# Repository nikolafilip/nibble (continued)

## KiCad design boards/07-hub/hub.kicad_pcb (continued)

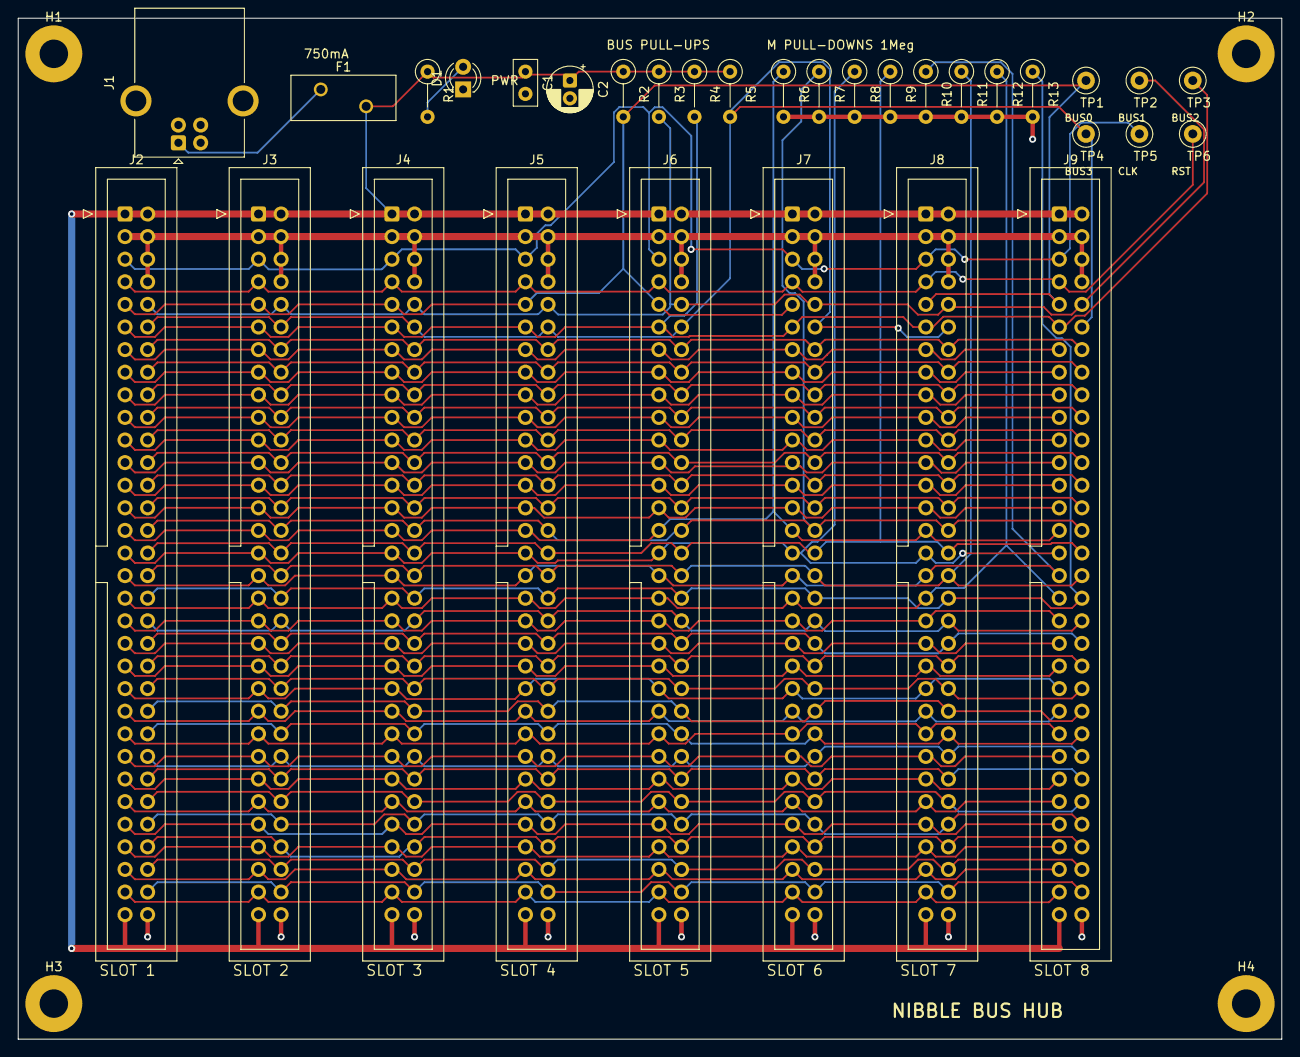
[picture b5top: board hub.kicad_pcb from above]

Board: 2 copper layers, 142.0 x 114.7 mm, 36 parts (0 on the bottom side), 60 nets.

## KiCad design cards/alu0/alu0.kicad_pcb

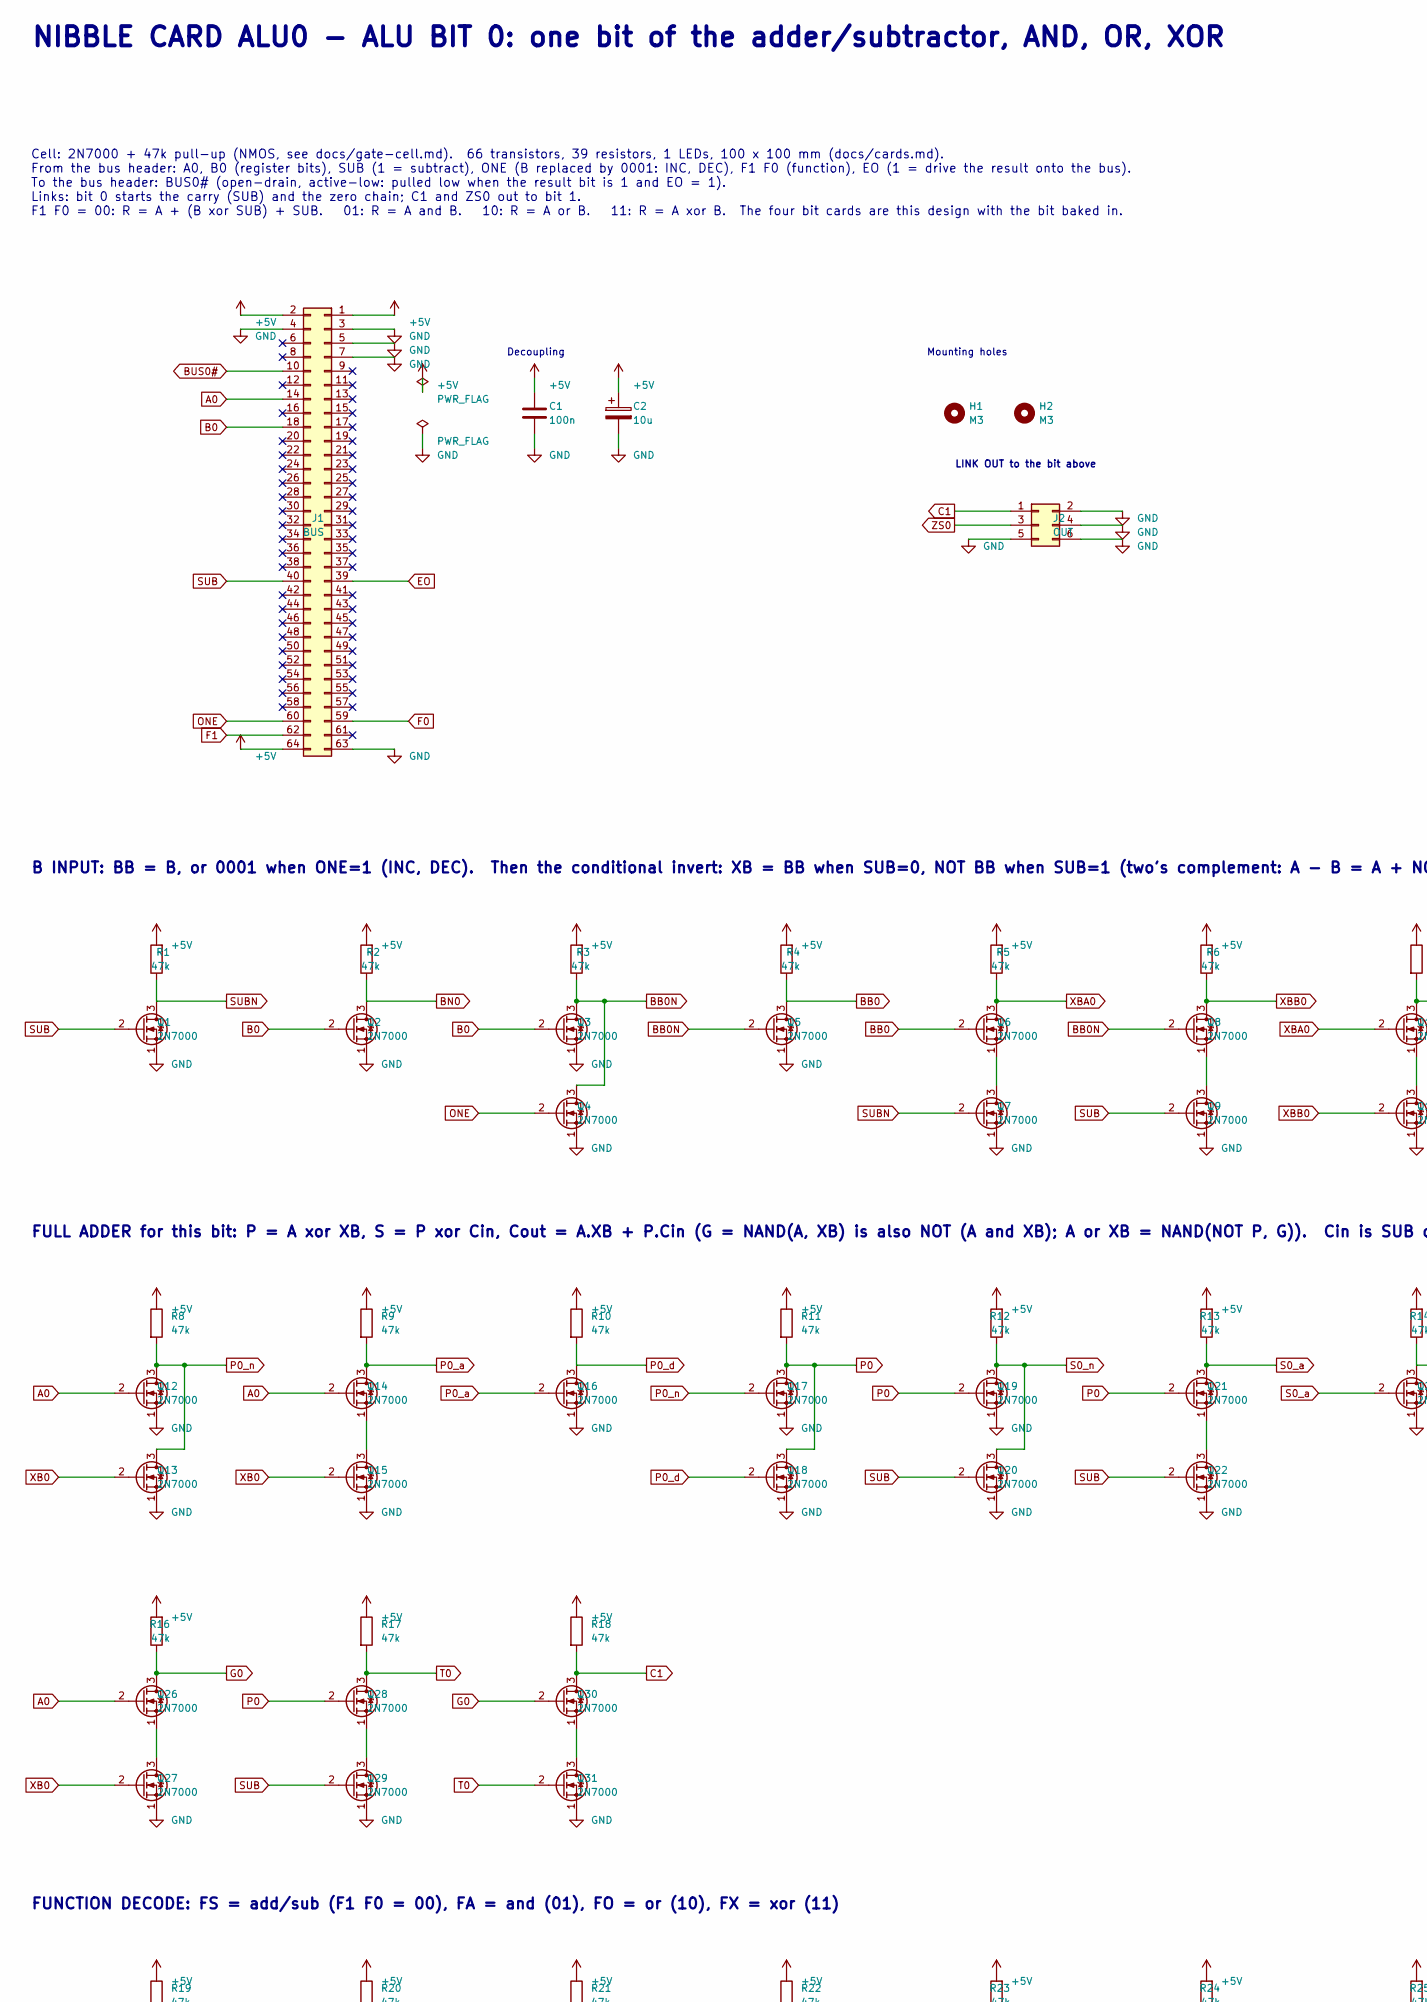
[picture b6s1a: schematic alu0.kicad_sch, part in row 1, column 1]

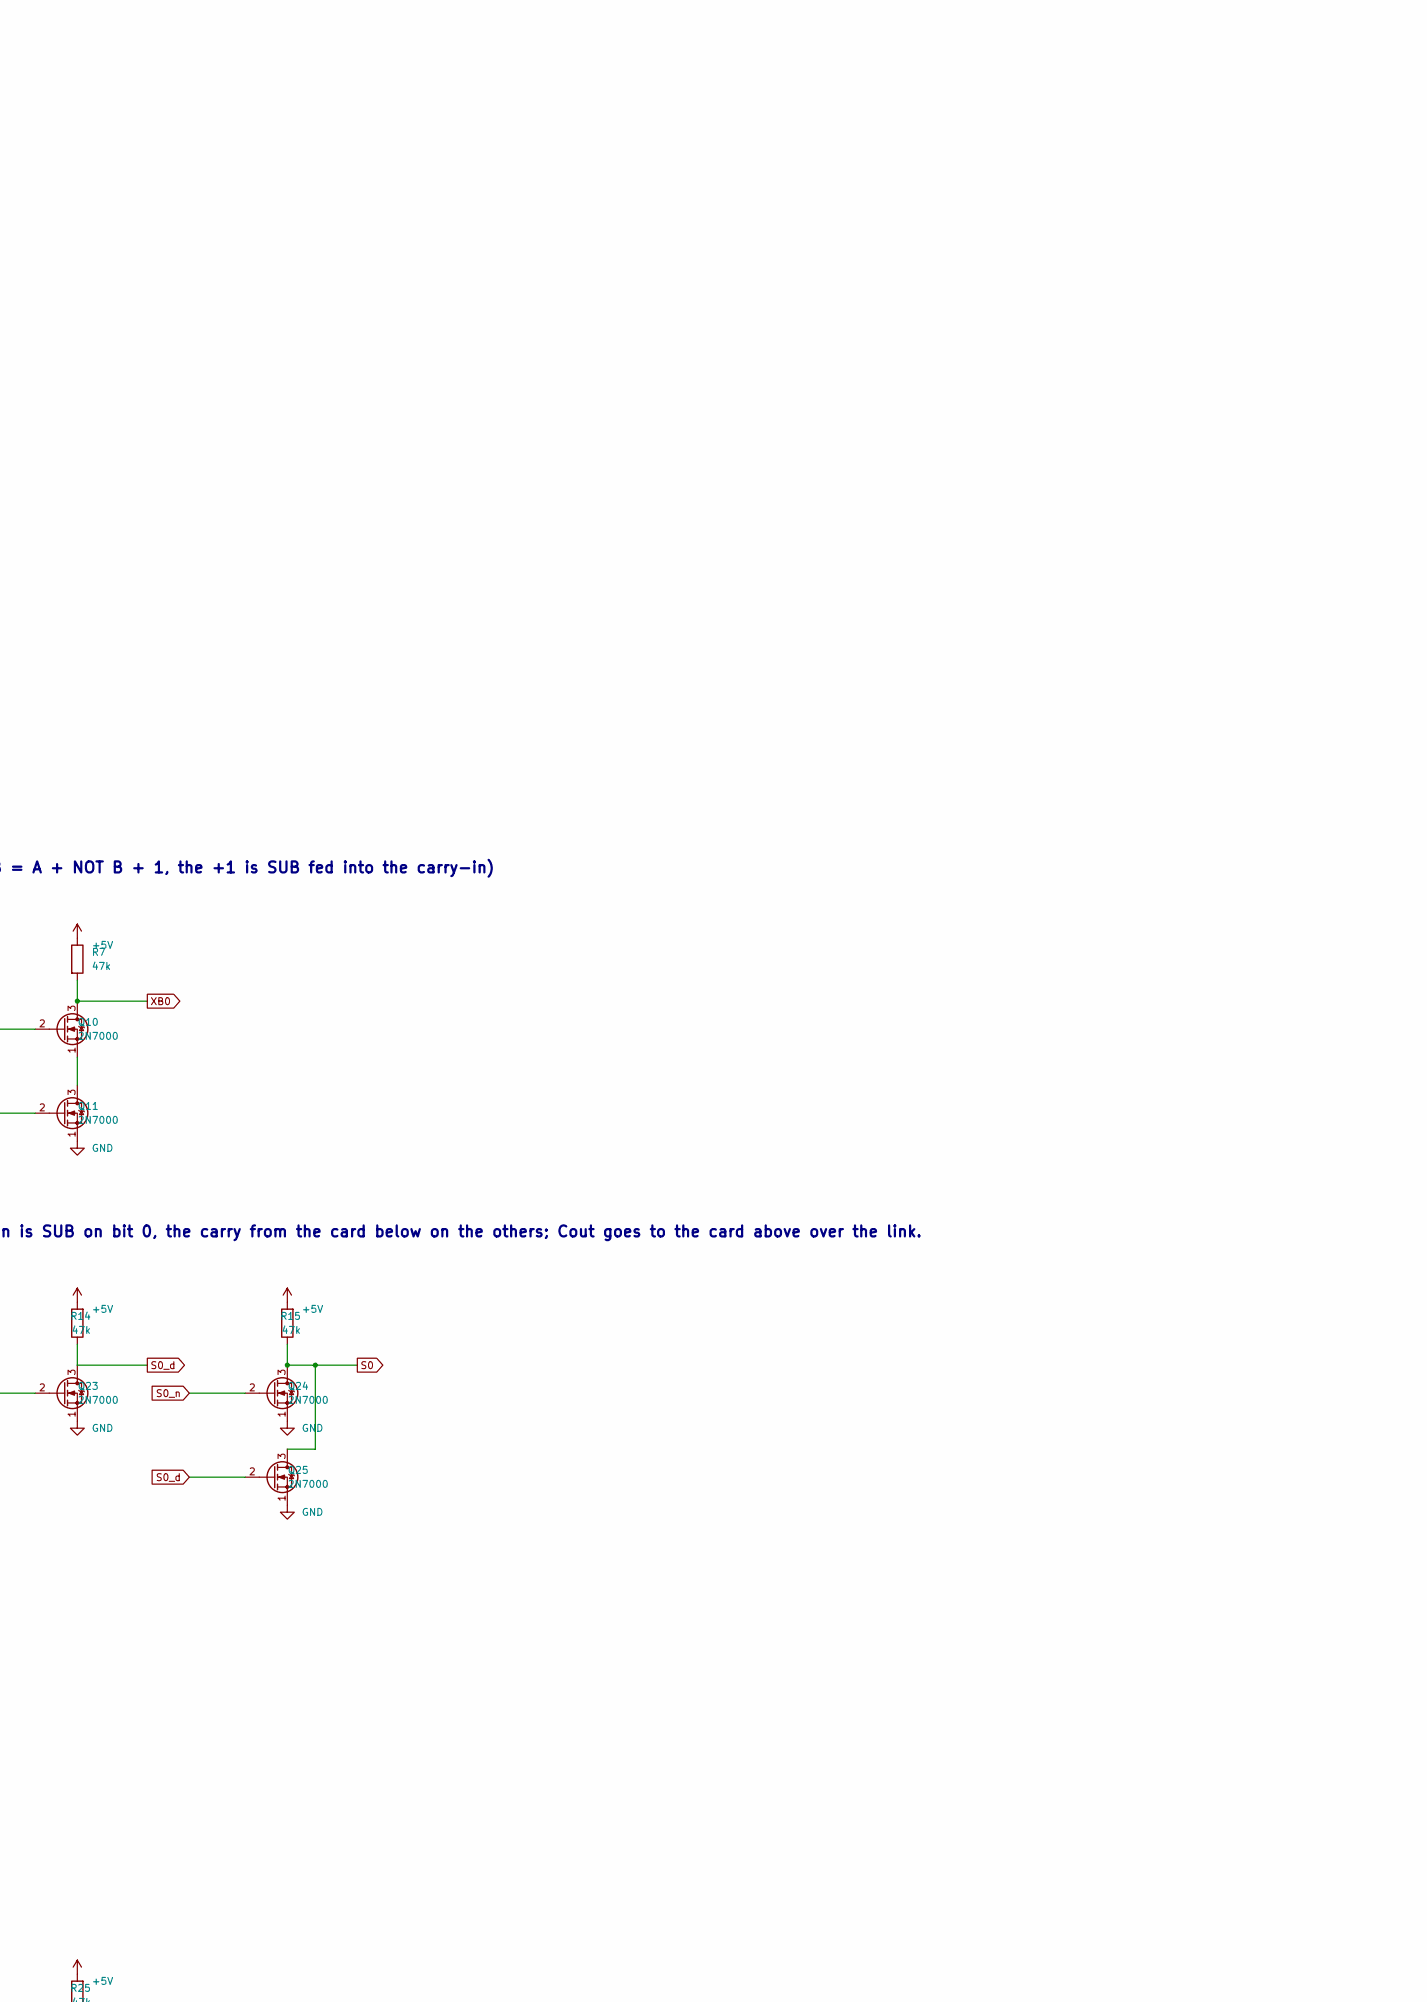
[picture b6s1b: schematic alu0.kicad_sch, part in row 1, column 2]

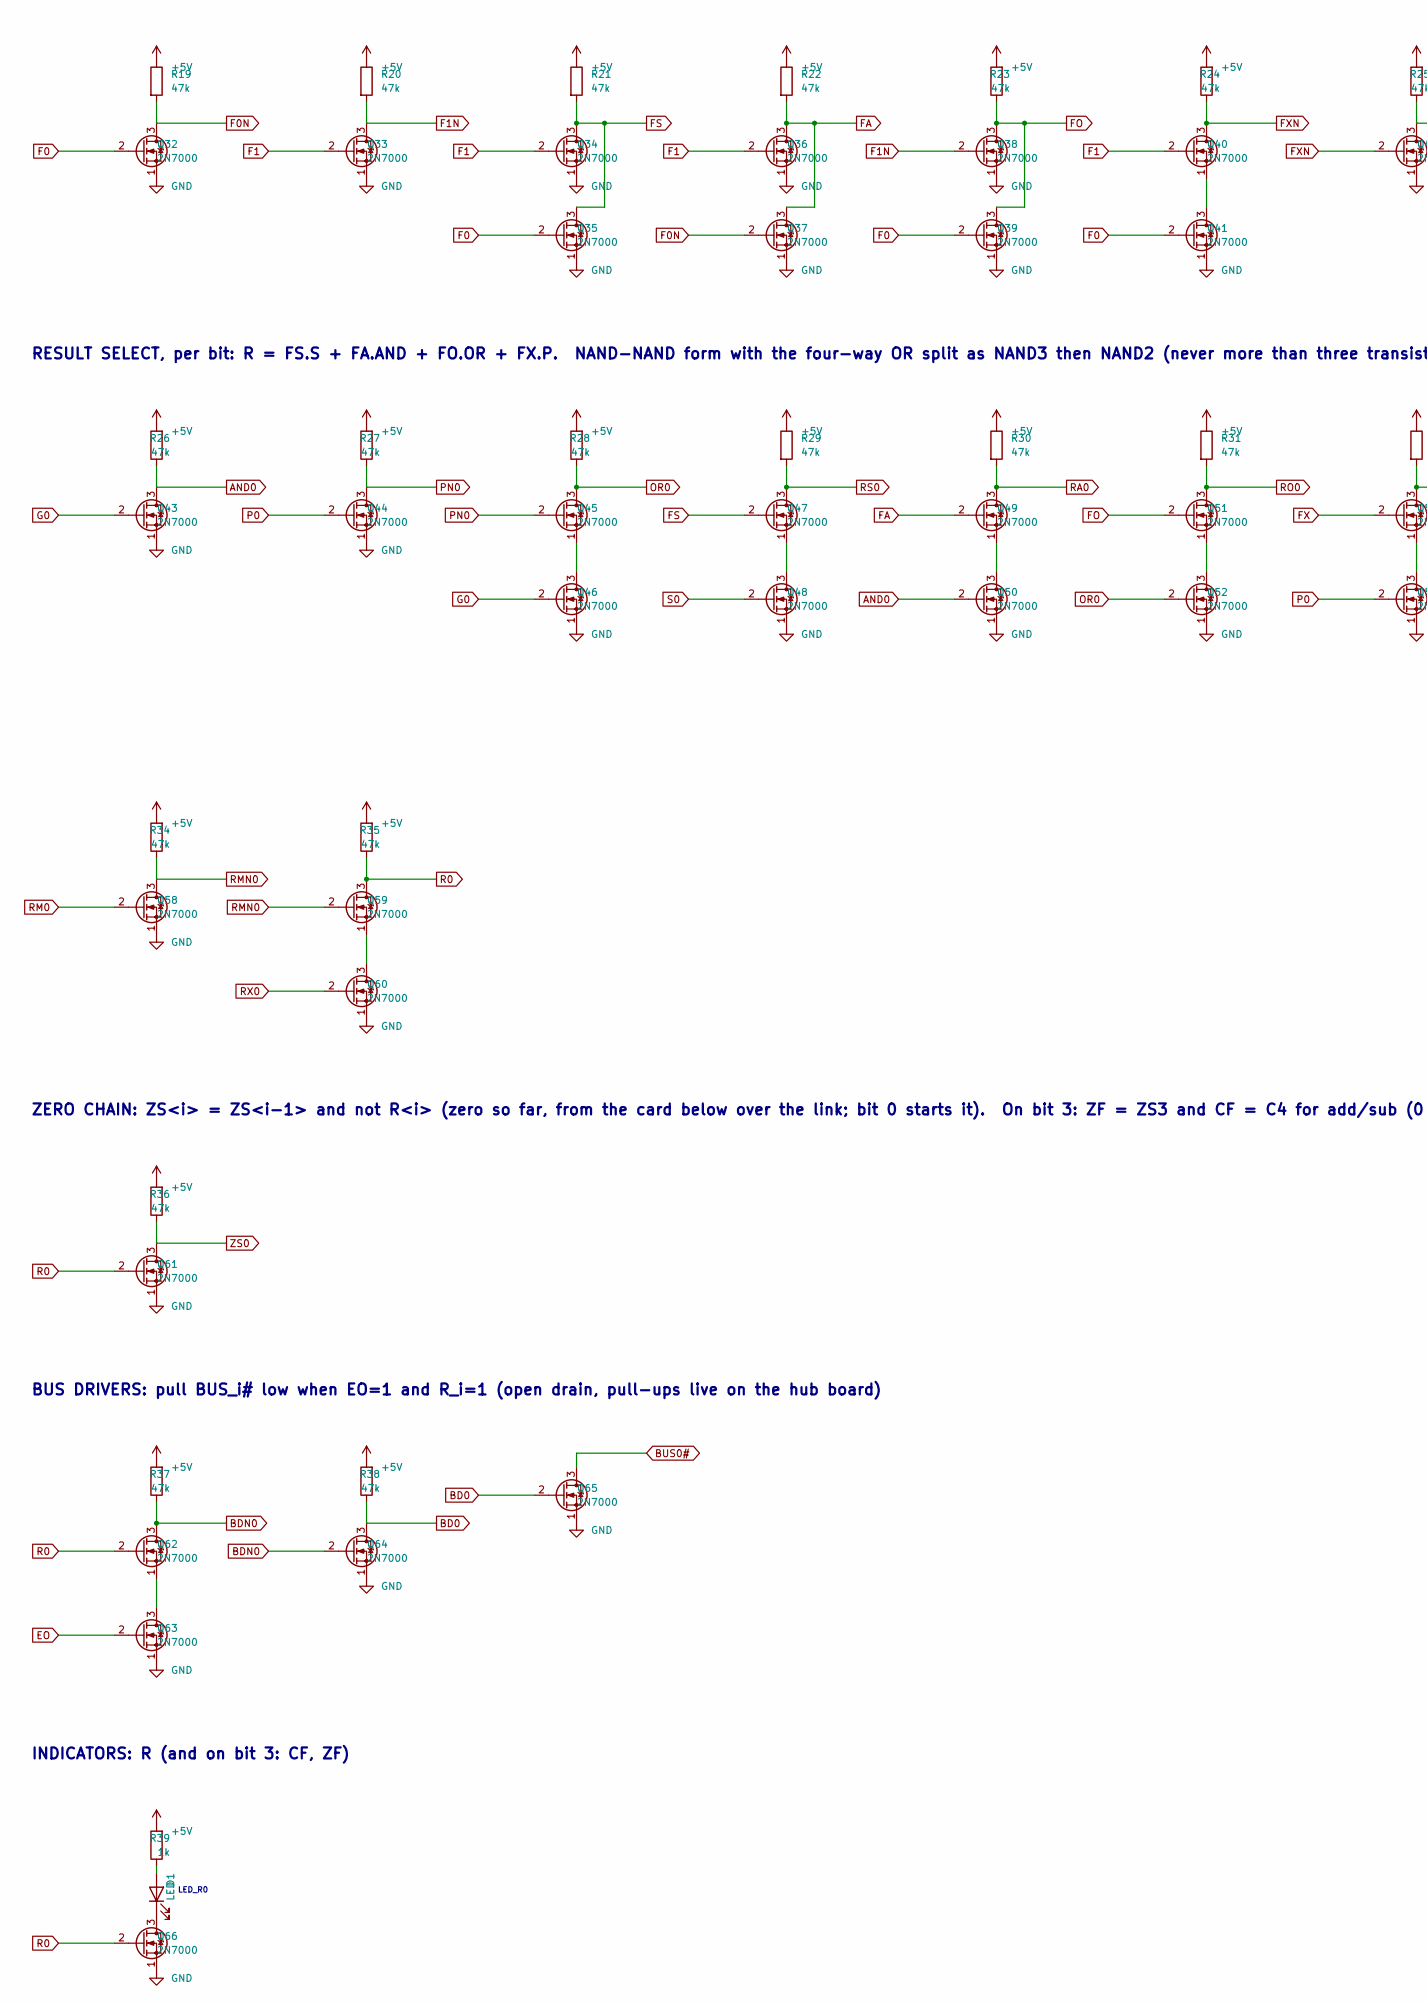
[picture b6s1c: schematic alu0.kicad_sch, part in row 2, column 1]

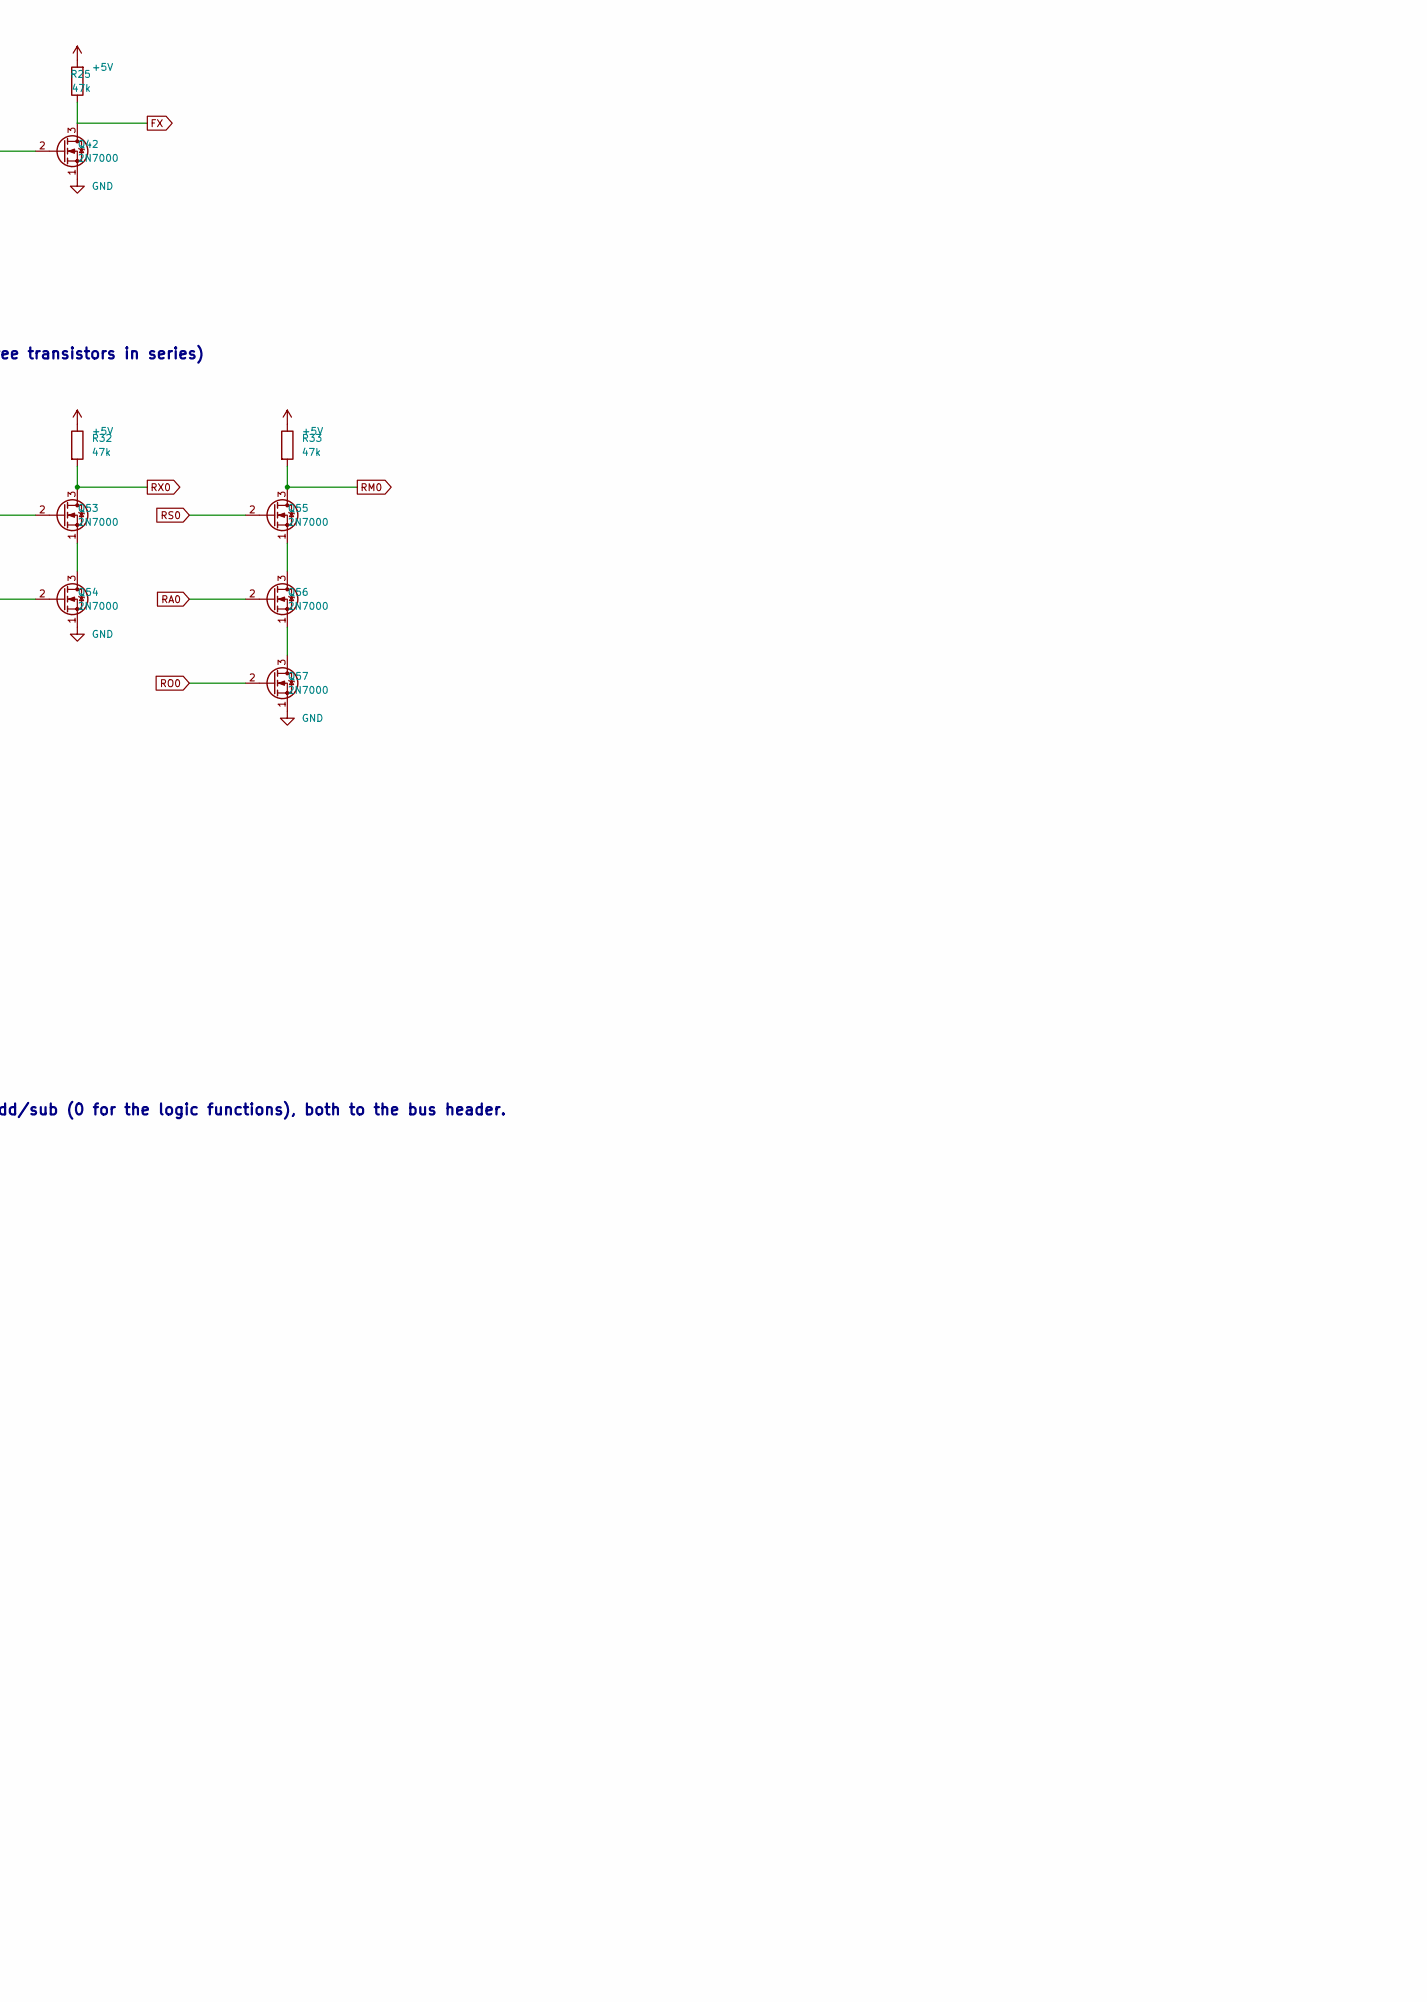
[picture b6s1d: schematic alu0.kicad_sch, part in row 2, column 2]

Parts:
C1: 100n; C_Disc_D5.0mm_W2.5mm_P2.50mm
C2: 10u; CP_Radial_D5.0mm_P2.00mm
D1: LED; LED_D3.0mm
H1, H2: M3; MountingHole_3.2mm_M3_Pad
J1: BUS; IDC-Header_2x32_P2.54mm_Vertical
J2: OUT; IDC-Header_2x03_P2.54mm_Vertical
Q1, Q2, Q3, Q4, Q5, Q6, Q7, Q8, Q9, Q10, Q11, Q12, Q13, Q14, Q15, Q16, Q17, Q18, Q19, Q20, Q21, Q22, Q23, Q24, Q25, Q26, Q27, Q28, Q29, Q30, Q31, Q32, Q33, Q34, Q35, Q36, Q37, Q38, Q39, Q40, Q41, Q42, Q43, Q44, Q45, Q46, Q47, Q48, Q49, Q50, Q51, Q52, Q53, Q54, Q55, Q56, Q57, Q58, Q59, Q60, Q61, Q62, Q63, Q64, Q65, Q66: 2N7000; TO-92_Inline_Wide
R1, R2, R3, R4, R5, R6, R7, R8, R9, R10, R11, R12, R13, R14, R15, R16, R17, R18, R19, R20, R21, R22, R23, R24, R25, R26, R27, R28, R29, R30, R31, R32, R33, R34, R35, R36, R37, R38: 47k; R_Axial_DIN0207_L6.3mm_D2.5mm_P5.08mm_Vertical
R39: 1k; R_Axial_DIN0207_L6.3mm_D2.5mm_P5.08mm_Vertical

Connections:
+5V: C1.1, C2.1, J1.1, J1.2, J1.64, R1.2, R2.2, R3.2, R4.2, R5.2, R6.2, R7.1, R8.1, R9.1, R10.1, R11.1, R12.2, R13.2, R14.2, R15.2, R16.2, R17.1, R18.1, R19.1, R20.1, R21.1, R22.1, R23.2, R24.2, R25.2, R26.2, R27.2, R28.2, R29.1, R30.1, R31.1, R32.1, R33.1, R34.2, R35.2, R36.2, R37.2, R38.2, R39.2
A0: J1.14, Q12.2 (G), Q14.2 (G), Q26.2 (G)
AND0: Q43.3 (D), Q50.2 (G), R26.1
B0: J1.18, Q2.2 (G), Q3.2 (G)
BB0: Q5.3 (D), Q6.2 (G), R4.1
BB0N: Q3.3 (D), Q4.3 (D), Q5.2 (G), Q8.2 (G), R3.1
BD0: Q64.3 (D), Q65.2 (G), R38.1
BDN0: Q62.3 (D), Q64.2 (G), R37.1
BN0: Q2.3 (D), R2.1
BUS0#: J1.10, Q65.3 (D)
C1: J2.1, Q30.3 (D), R18.2
EO: J1.39, Q63.2 (G)
F0: J1.59, Q32.2 (G), Q35.2 (G), Q39.2 (G), Q41.2 (G)
F0N: Q32.3 (D), Q37.2 (G), R19.2
F1: J1.62, Q33.2 (G), Q34.2 (G), Q36.2 (G), Q40.2 (G)
F1N: Q33.3 (D), Q38.2 (G), R20.2
FA: Q36.3 (D), Q37.3 (D), Q49.2 (G), R22.2
FO: Q38.3 (D), Q39.3 (D), Q51.2 (G), R23.1
FS: Q34.3 (D), Q35.3 (D), Q47.2 (G), R21.2
FX: Q42.3 (D), Q53.2 (G), R25.1
FXN: Q40.3 (D), Q42.2 (G), R24.1
G0: Q26.3 (D), Q30.2 (G), Q43.2 (G), Q46.2 (G), R16.1
GND: C1.2, C2.2, J1.3, J1.4, J1.5, J1.7, J1.63, J2.2, J2.4, J2.5, J2.6, Q1.1 (S), Q2.1 (S), Q3.1 (S), Q4.1 (S), Q5.1 (S), Q7.1 (S), Q9.1 (S), Q11.1 (S), Q12.1 (S), Q13.1 (S), Q15.1 (S), Q16.1 (S), Q17.1 (S), Q18.1 (S), Q19.1 (S), Q20.1 (S), Q22.1 (S), Q23.1 (S), Q24.1 (S), Q25.1 (S), Q27.1 (S), Q29.1 (S), Q31.1 (S), Q32.1 (S), Q33.1 (S), Q34.1 (S), Q35.1 (S), Q36.1 (S), Q37.1 (S), Q38.1 (S), Q39.1 (S), Q41.1 (S), Q42.1 (S), Q43.1 (S), Q44.1 (S), Q46.1 (S), Q48.1 (S), Q50.1 (S), Q52.1 (S), Q54.1 (S), Q57.1 (S), Q58.1 (S), Q60.1 (S), Q61.1 (S), Q63.1 (S), Q64.1 (S), Q65.1 (S), Q66.1 (S)
unnamed: D1.2 (A), R39.1
unnamed: D1.1 (K), Q66.3 (D)
unnamed: Q6.1 (S), Q7.3 (D)
unnamed: Q8.1 (S), Q9.3 (D)
unnamed: Q10.1 (S), Q11.3 (D)
unnamed: Q14.1 (S), Q15.3 (D)
unnamed: Q21.1 (S), Q22.3 (D)
unnamed: Q26.1 (S), Q27.3 (D)
unnamed: Q28.1 (S), Q29.3 (D)
unnamed: Q30.1 (S), Q31.3 (D)
unnamed: Q40.1 (S), Q41.3 (D)
unnamed: Q45.1 (S), Q46.3 (D)
unnamed: Q47.1 (S), Q48.3 (D)
unnamed: Q49.1 (S), Q50.3 (D)
unnamed: Q51.1 (S), Q52.3 (D)
unnamed: Q53.1 (S), Q54.3 (D)
unnamed: Q55.1 (S), Q56.3 (D)
unnamed: Q56.1 (S), Q57.3 (D)
unnamed: Q59.1 (S), Q60.3 (D)
unnamed: Q62.1 (S), Q63.3 (D)
ONE: J1.60, Q4.2 (G)
OR0: Q45.3 (D), Q52.2 (G), R28.1
P0: Q17.3 (D), Q18.3 (D), Q19.2 (G), Q21.2 (G), Q28.2 (G), Q44.2 (G), Q54.2 (G), R11.2
P0_a: Q14.3 (D), Q16.2 (G), R9.2
P0_d: Q16.3 (D), Q18.2 (G), R10.2
P0_n: Q12.3 (D), Q13.3 (D), Q17.2 (G), R8.2
PN0: Q44.3 (D), Q45.2 (G), R27.1
R0: Q59.3 (D), Q61.2 (G), Q62.2 (G), Q66.2 (G), R35.1
RA0: Q49.3 (D), Q56.2 (G), R30.2
RM0: Q55.3 (D), Q58.2 (G), R33.2
RMN0: Q58.3 (D), Q59.2 (G), R34.1
RO0: Q51.3 (D), Q57.2 (G), R31.2
RS0: Q47.3 (D), Q55.2 (G), R29.2
RX0: Q53.3 (D), Q60.2 (G), R32.2
S0: Q24.3 (D), Q25.3 (D), Q48.2 (G), R15.1
S0_a: Q21.3 (D), Q23.2 (G), R13.1
S0_d: Q23.3 (D), Q25.2 (G), R14.1
S0_n: Q19.3 (D), Q20.3 (D), Q24.2 (G), R12.1
SUB: J1.40, Q1.2 (G), Q9.2 (G), Q20.2 (G), Q22.2 (G), Q29.2 (G)
SUBN: Q1.3 (D), Q7.2 (G), R1.1
T0: Q28.3 (D), Q31.2 (G), R17.2
XB0: Q10.3 (D), Q13.2 (G), Q15.2 (G), Q27.2 (G), R7.2
XBA0: Q6.3 (D), Q10.2 (G), R5.1
XBB0: Q8.3 (D), Q11.2 (G), R6.1
ZS0: J2.3, Q61.3 (D), R36.1

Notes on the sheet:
NIBBLE CARD ALU0 - ALU BIT 0: one bit of the adder/subtractor, AND, OR, XOR
Cell: 2N7000 + 47k pull-up (NMOS, see docs/gate-cell.md). 66 transistors, 39 resistors, 1 LEDs, 100 x 100 mm (docs/cards.md). From the bus header: A0, B0 (register bits), SUB (1 = subtract), ONE (B replaced by 0001: INC, DEC), F1 F0 (function), EO (1 = drive the result onto the bus). To the bus hea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
B INPUT: BB = B, or 0001 when ONE=1 (INC, DEC). Then the conditional invert: XB = BB when SUB=0, NOT BB when SUB=1 (two's complement: A - B = A + NOT B + 1, the +1 is SUB fed into the carry-in)
FULL ADDER for this bit: P = A xor XB, S = P xor Cin, Cout = A.XB + P.Cin (G = NAND(A, XB) is also NOT (A and XB); A or XB = NAND(NOT P, G)). Cin is SUB on bit 0, the carry from the card below on the others; Cout goes to the card above over the link.
FUNCTION DECODE: FS = add/sub (F1 F0 = 00), FA = and (01), FO = or (10), FX = xor (11)
RESULT SELECT, per bit: R = FS.S + FA.AND + FO.OR + FX.P. NAND-NAND form with the four-way OR split as NAND3 then NAND2 (never more than three transistors in series)
ZERO CHAIN: ZS<i> = ZS<i-1> and not R<i> (zero so far, from the card below over the link; bit 0 starts it). On bit 3: ZF = ZS3 and CF = C4 for add/sub (0 for the logic functions), both to the bus header.
BUS DRIVERS: pull BUS_i# low when EO=1 and R_i=1 (open drain, pull-ups live on the hub board)
INDICATORS: R (and on bit 3: CF, ZF)
LED_R0
Decoupling
Mounting holes
LINK OUT to the bit above

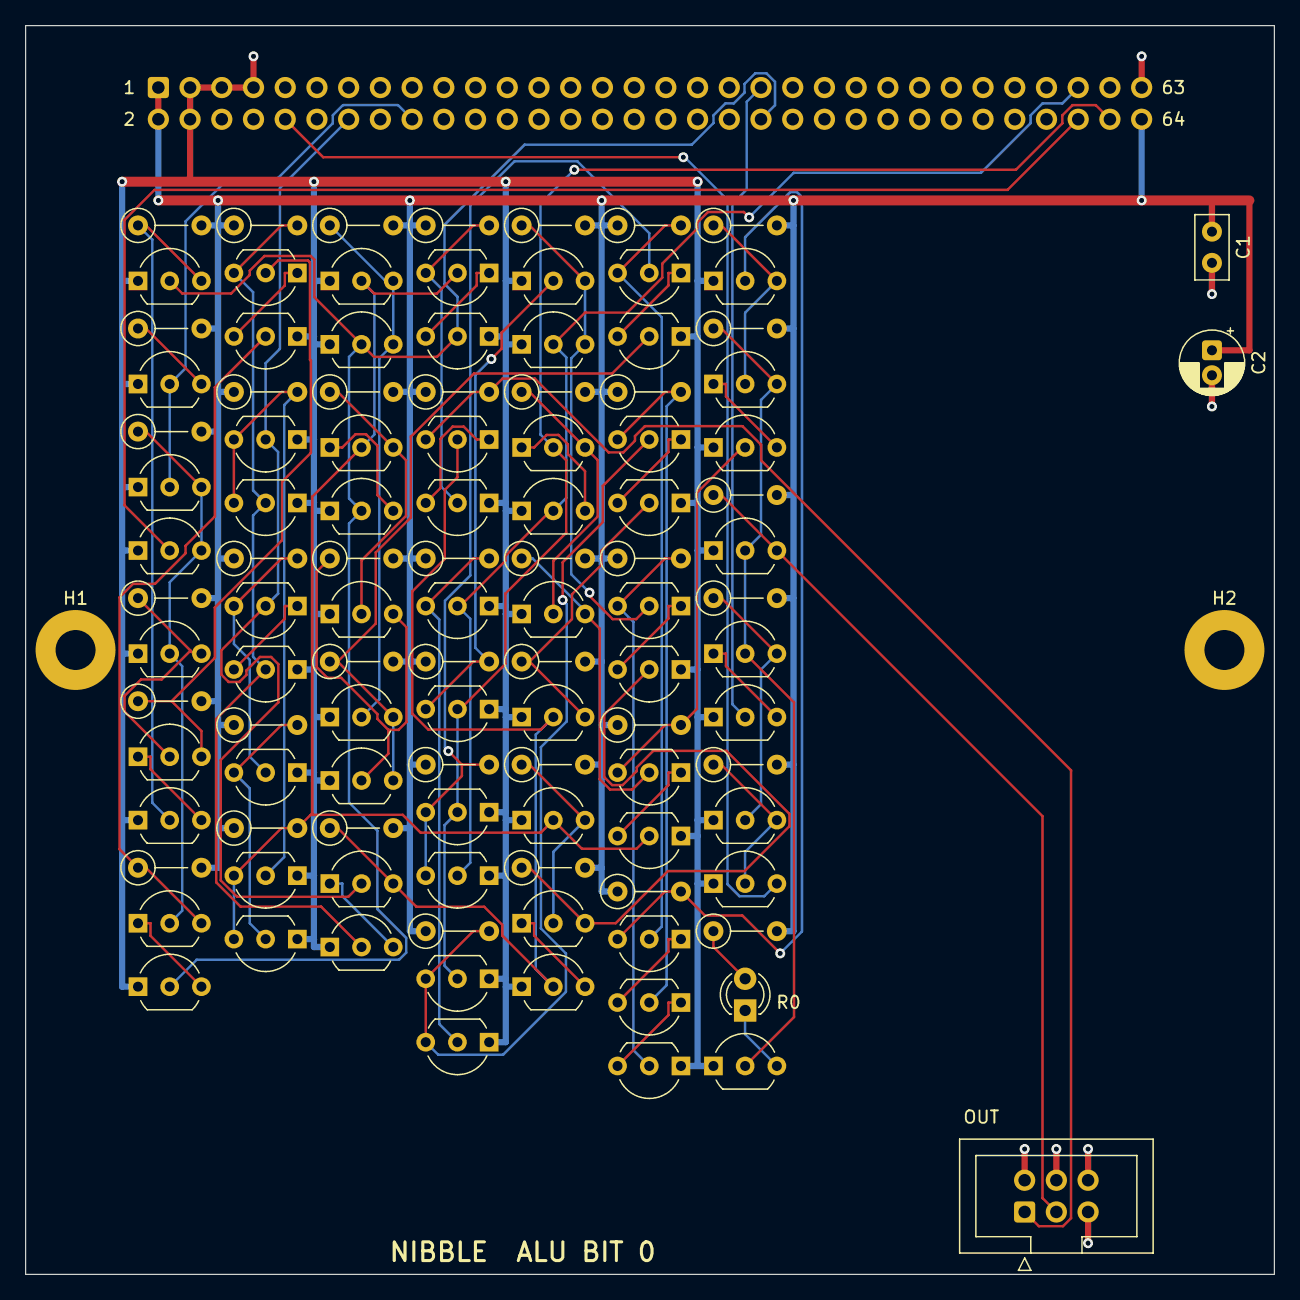
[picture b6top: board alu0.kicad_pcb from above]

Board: 2 copper layers, 100.0 x 100.0 mm, 112 parts (1 on the bottom side), 68 nets.
